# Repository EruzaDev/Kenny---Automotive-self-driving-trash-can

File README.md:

# KENNY lightweight RL environment

A runnable Gymnasium navigation simulator and PPO training pipeline for a small indoor robot. It uses height-aware boxes and analytical sensor rays instead of a full physics/rendering engine, so the laptop does not need Gazebo, ROS, or GPU rendering during training.

**This is a training environment, not a validated autonomous robot controller.** The simulator approximates LiDAR, depth, marker localization and wheel motion. Use it for learning and debugging, then validate in Gazebo and on guarded hardware before deployment. The current ROS/robot roadmap is in [the robot setup guide](docs/RL_TRAINING_AND_ROBOT_GUIDE.md).

The [0.60, 0.80, and 1.00 m/s simulation checkpoints](runs/faster-noise-moving-pilot-20261010/README.md) are included with their loading configs, contracts, and test reports. Use `speed_100/best_guarded.zip` for the 1.00 m/s map preview; see the checkpoint notes for the separate relaxed-cruise editor mode.

For Raspberry Pi 5, follow the [installation and live 3D depth GUI guide](docs/PI5_SETUP.md). The [tested Pi status](docs/PI5_SETUP_STATUS.md) records measured results and remaining hardware issues.

For ESP32-WROOM with four encoder gearmotors and two L298N boards, see the [firmware and wiring guide](docs/ESP32_FIRMWARE.md).

For phone control over the ESP32's own Wi-Fi, use the [mobile joystick firmware and setup guide](docs/ESP32_MOBILE_CONTROLLER.md). Select direct-GPIO or carrier-PCB wiring before upload.

The [provisional Kenny carrier PCB](hardware/kenny_carrier/README.md) adds four encoder terminal blocks, MPU6050/HX711 headers, passive components and labeled silkscreen. Its module footprint needs verification; the mobile sketch supports its MCP23017 motor interface when carrier mode is selected.

## Your robot

| Parameter | Configured value |
| --- | --- |
| Body width × length | 0.23 × 0.23 m |
| Total height | 0.485 m |
| Wheel track | 0.235 m, interpreted as wheel-center to wheel-center |
| Wheel diameter | 0.080 m |
| Gearmotor | 333 RPM JGB37-520; nominal wheel surface speed ≈1.395 m/s |
| Policy speed limits | 0–0.30 m/s, ±0.60 rad/s |
| Control rate | 10 Hz |
| LiDAR approximation | Horizontal scan at provisional 0.22 m height; 72 angular bins |
| Depth approximation | 36 horizontal × 9 vertical rays, reduced to collision-height ranges |
| Markers | Floor landmarks with visibility, occlusion, missed detections and noisy pose fixes |

**Confirm whether 23.5 cm is wheel-center spacing or the gap between tyre inner edges.** Camera mounting (provisionally 0.40 m high), field of view, ranges, sensor rate, acceleration and braking are configurable assumptions, not verified X3 Pro/Astra Pro calibration values. The robot collision footprint is a conservative circle enclosing the square body. Measure wheel protrusions and caster extent too.

## Install on the laptop

Supported Python: **3.10–3.12**. The system Python on this machine is 3.14, so use the separate Python 3.10 interpreter. From this repository, using `uv`:

```bash
uv venv --python python3.10 .venv
uv pip install --python .venv/bin/python torch==2.5.1 --index-url https://download.pytorch.org/whl/cpu
uv pip install --python .venv/bin/python -e '.[train,view,test]'
source .venv/bin/activate
```

A `.venv` with these packages has already been created in this workspace. On a fresh machine without `uv`, create a standard venv with `python3.10 -m venv .venv`, activate it, then use `python -m pip install` in place of `uv pip install --python .venv/bin/python`.

The CPU wheel avoids installing a large CUDA stack on your 8 GB laptop. SB3 specifically recommends CPU execution for small PPO MLPs; the RTX 2050 is optional here. Pinning PyTorch 2.5.1, SB3 2.4.1 and Gymnasium 1.0.0 keeps the tested API combination reproducible. [SB3 PPO guidance](https://stable-baselines3.readthedocs.io/en/master/modules/ppo.html), [PyTorch version-specific installers](https://pytorch.org/get-started/previous-versions/)

## Preview and validate

```bash
# Windowed top-down view: debug route follower, not a trained agent.
python -m kenny_rl.demo --stage full --seed 42

# No window required; creates a PNG.
python -m kenny_rl.demo --stage full --snapshot artifacts/world.png

# Headless speed/RAM check, followed by functional tests.
python -m kenny_rl.benchmark --steps 1000 --stage full
python -m pytest -q

# A very short end-to-end installation check, NOT navigation training.
python -m kenny_rl.train --config configs/smoke.json --run runs/my-smoke
```

You can also request a specific goal, for example:

```bash
python -m kenny_rl.demo --stage empty --start 1 1 --goal 8 9 --steps 1200
```

Coordinates are meters from the synthetic room's lower-left boundary; `(0,0)` is a wall corner here, so the robot cannot spawn there. Your real marker-map origin can be elsewhere: translate the site map and landmarks consistently. Custom points are rejected if occupied; connectivity is guaranteed for generated missions, but not for arbitrary manual goals.

In the view: grey = walls, teal = chairs, brown = low bags, purple = overhangs, orange = moving people, black/red = floor gaps, yellow squares = markers, blue circle = robot, red cross = estimated position, green star = goal. The drawn route is computed from the structural map and observed hazards; it can initially cross unseen clutter or a hidden drop.

Rendering is optional and off in all training workers. For a headless machine with an unwritable home cache, set `MPLCONFIGDIR=/tmp/kenny-mpl` before creating a snapshot.

## Train progressively

Start with one environment and the laptop configuration:

```bash
python -m kenny_rl.train --config configs/laptop.json --run runs/empty-0 --stage empty --steps 100000 --seed 0
```

This is a starting experiment budget, not an assertion that 100,000 transitions will converge. Look at validation success, collisions, timeouts and interventions. Train longer if necessary; do not advance merely because the command finished.

Resume the actor/critic and optimizer into a **new** output directory. The environment's random episode stream starts from the new seed, so this is training continuation, not bit-for-bit mid-episode replay:

```bash
python -m kenny_rl.train --config configs/laptop.json --run runs/static-0 --resume runs/empty-0/final.zip --stage static --steps 200000 --seed 0
```

Proceed through these stages, retaining and evaluating earlier checkpoints:

| Stage | What the world contains |
| --- | --- |
| `empty` | Room boundary; shorter randomized goals |
| `static` | Blocks, wall openings, turns and detours |
| `mixed` | Static layouts plus chair parts, low bags and hanging obstacles |
| `dynamic` | Mixed layouts plus walking people and periodically moved/placed bags |
| `cliffs` | Mixed layouts plus unsupported floor patches |
| `full` | All obstacle types, people, changing clutter and floor gaps |

All stages randomize positions and start/goal headings. Full worlds vary in size, layout, obstacle combinations, motor gain, slip, command delay and acceleration response. Sensor noise/dropouts and marker occlusion remain active. The curriculum is **manual**, not an automatic stage scheduler; evaluate simpler stages again to catch forgetting. Three or more independent training seeds are recommended.

For the requested larger layouts, train separate policies (or fine-tune sequentially) with the included configurations:

```bash
# 21 m × 21 m square
python -m kenny_rl.train --config configs/server_21x21.json --run runs/full-21x21-0 --seed 0

# 21 m × 10 m rectangle
python -m kenny_rl.train --config configs/server_21x10.json --run runs/full-21x10-0 --seed 0
```

`world_width` and `world_height` set the generated room axes. They default to `world_size` when absent, so older square configurations still behave unchanged. The size randomization is applied uniformly to both axes, preserving the room's aspect ratio.

### Continue reviewed mixed-stage policies on larger rooms

Use `server_mixed_21x21.json` and `server_mixed_21x10.json` to adapt existing
mixed-stage policies without simultaneously introducing pedestrians or cliffs.
These profiles preserve the avoidance reward, clearance cost, 20% simulation-only
unshielded training mixture, and paired guarded/unshielded validation. Each run
adds 250,000 transitions, with 30 validation episodes per mode every 25,000
transitions, seven workers per learner, and a 1,800-step episode limit. Dimensions
are nominal: domain randomization still varies both axes together by ±15%.

On the server, activate the training virtual environment and work from the repo
root. Ensure the previous training sweep has exited and your allocation grants
four GPUs and 32 CPUs. Use a persistent terminal such as `tmux`; detaching keeps
the launcher's session open, but does not extend a scheduler allocation.

```bash
python scripts/server_sweep.py \
  --config configs/server_mixed_21x21.json \
  --resume-from runs/server-mixed-v3-reviewed-all-gpus-continued \
  --resume-checkpoint best_guarded.zip \
  --output runs/server-mixed-21x21-reviewed \
  --seeds 0 1 2 3 --devices cuda:0 cuda:1 cuda:2 cuda:3 \
  --cpu-budget 32 --envs 7 --stage mixed --steps 250000
```

Append `--dry-run` to check all four resume artifacts/contracts without launching.
The reviewed directory contains `best_guarded.zip` for every seed; no placeholder
path or missing final checkpoint is needed. This selects each seed's guarded
best, not necessarily its newest checkpoint. Do not disable the shield on hardware.

After that sweep exits successfully, train the rectangular layout independently
from the same source checkpoints (do not run both four-GPU sweeps simultaneously):

```bash
python scripts/server_sweep.py \
  --config configs/server_mixed_21x10.json \
  --resume-from runs/server-mixed-v3-reviewed-all-gpus-continued \
  --resume-checkpoint best_guarded.zip \
  --output runs/server-mixed-21x10-reviewed \
  --seeds 0 1 2 3 --devices cuda:0 cuda:1 cuda:2 cuda:3 \
  --cpu-budget 32 --envs 7 --stage mixed --steps 250000
```

Monitor from another terminal, regardless of its working directory:

```bash
tail -n 30 -F ~/Kenny---Automotive-self-driving-trash-can/runs/server-mixed-21x21-reviewed/seed_{0,1,2,3}.log
```

Change `21x21` to `21x10` when monitoring the rectangular sweep. Output directories
must be new; the launcher refuses to overwrite one. Initial paired validation
can take several minutes before rollout tables appear. These profiles change room
size and episode budget; they do not fix the previously observed sensor-coverage
deadlocks or obstacle-command loops. Evaluate held-out worlds before deployment.

Runs contain:

- `final.zip`, periodic `checkpoints/`, and `best.zip` after the first validation.
- `config.json`, `contract.json`, dependency versions, seed and source hashes.
- `validation.jsonl` with per-episode results and aggregate metrics before training,
  periodically during training, and after the final PPO update. The final record
  can share a timestep count with a periodic record scored before that update.
- TensorBoard events, viewable with `tensorboard --logdir runs`.

`best.zip` ranks success first, then observed collision/cliff rates, intervention
fraction and reward. Dual validation selects by performance in both guarded and
unshielded modes and retains a separate `best_guarded.zip`. Small validation
samples are noisy; inspect records before selecting a release candidate.
Ctrl+C or SIGTERM during PPO training saves `interrupted.zip` and exits with
status 130. Existing run directories are rejected to avoid overwriting
experiments. Resume rejects changed robot/observation contracts; start fresh
after changing physical dimensions or sensor feature layout.

Training settings are checked before workers start; unknown settings, invalid
counts and nonfinite values are rejected. Nonfinite observations, actions or
rewards abort training rather than silently propagating through PPO. Behavior
cloning keeps demonstrations in CPU memory and transfers each minibatch to the
training device.

## Evaluate new layouts and dynamic changes

```bash
python -m kenny_rl.evaluate --model runs/static-0/final.zip --split test --stage full --episodes 100 --output artifacts/test-full.json
python -m kenny_rl.evaluate --model runs/static-0/final.zip --split stress --stage full --episodes 100 --output artifacts/stress-full.json

# Simulation-only ablation: reveals how much the guard rescues the policy.
python -m kenny_rl.evaluate --model runs/static-0/final.zip --split test --stage full --episodes 100 --unshielded --output artifacts/unshielded.json

# Watch a trained checkpoint in a newly generated world.
python -m kenny_rl.demo --model runs/static-0/final.zip --stage full --seed 700
```

The example paths must point to checkpoints you actually trained. A static-only policy is not expected to pass the full test suite; these commands illustrate how to reveal that gap.

Train/validation/test use distinct seeded random streams. Stress testing additionally introduces larger worlds and U-shaped traps not included in the training generator. A change in seed is not proof of real-world generalization; use measured school layouts in later Gazebo tests. Do not tune on the final test seeds.

A successful run must reach the goal and slow down; wall contact, cliff entry and timeouts are separate outcomes. Reports include localization error, traveled distance, interventions and clutter changes. Inspect performance by stage, and count guarded collisions as failures. Run at least 500 held-out episodes across trained seeds before considering physical validation; zero observed falls in simulation is not a safety guarantee.

## Move to the school server

Copy the source, configurations, and the complete chosen run directory. Do not copy the laptop's `.venv`. Create a fresh Python 3.10–3.12 environment on the server and install the same package versions.

First test the CPU configuration, increasing from two workers to eight only after checking CPU availability and memory:

```bash
python -m kenny_rl.train --config configs/server.json --envs 2 --run runs/server-check --stage full --steps 4096
python -m kenny_rl.train --config configs/server.json --run runs/server-0 --resume runs/static-0/final.zip --stage full --steps 1000000
```

Server defaults: up to 8 spawned simulation workers per GPU learner, 512 rollout steps per worker, 512-sample minibatches, 2 conservative PPO epochs, and target KL 0.005. The sweep launcher defaults to four CUDA devices and four independent seeds, scales worker counts to CPU allocation, and checks CUDA before starting. Training is headless. See the [sim-to-real audit and server instructions](docs/SIM_TO_REAL_AUDIT.md) for disturbance settings, transfer gaps, installation and curriculum continuation.

**Four A5000s do not automatically accelerate a single SB3 PPO learner.** This implementation can run four independent seeds/experiments, one per device. It does not implement synchronous multi-GPU PPO, and the geometric simulator remains CPU-based. Start with one server job; check the school's scheduler/resource rules before launching more.

For a fresh server experiment, first learn basic goal reaching with
`configs/server_bootstrap.json`. It uses empty geometry without dynamics or
sensor disturbances and shorter episodes. Advance only after held-out validation
shows that PPO can stop at the goal. Then resume into `configs/server.json` on
the empty stage to add measured-motion surrogates, noise, dropout, delays and
outage bursts. `best.zip` prioritizes successful navigation, then observed
collision/cliff rate and intervention rate; release evaluation still requires
zero observed contacts.

For GPU experiments, install the matching CUDA build in a fresh server environment. The following is the official CUDA 12.4 wheel family for the pinned PyTorch version; first verify the server's NVIDIA driver supports it:

```bash
uv pip install --python .venv/bin/python torch==2.5.1 --index-url https://download.pytorch.org/whl/cu124
uv pip install --python .venv/bin/python -e '.[train,view,test]'
.venv/bin/python -c 'import torch; print(torch.cuda.is_available(), torch.cuda.device_count())'
```

Then preview the commands before scheduling a sweep:

```bash
python scripts/server_sweep.py --output runs/a5000-sweep --stage empty --dry-run
# When resources are allocated, repeat without --dry-run to execute.
```

The sweep starts independent runs from scratch, or continues per-seed checkpoints with `--resume-from runs/previous-sweep`. Eight workers plus one learner per GPU needs 36 CPU slots; on 32 allocated slots the launcher selects seven workers/run. Use `--cpu-budget` to specify a scheduler allocation not reflected in CPU affinity, or `--envs` for an explicit worker count. Use `--devices cpu` for sequential CPU seed experiments. Model weights are portable between CPU and CUDA. Start fresh with the v3 contract: older checkpoints are rejected because route progress, rewards and guard behavior changed.

### More than four independent training jobs

The default remains one learner per device. `--jobs-per-device 2` enables eight
simultaneous learners on four GPUs; extra seeds queue and use the next free slot.
CPU workers are budgeted across active slots, including configured Torch threads,
and idle slots are not reserved when there are fewer seeds. Output directories
must be new. Each seed has its own checkpoints and log; `sweep.json` records actual
device assignments. No existing run or model is overwritten.

```bash
python scripts/server_sweep.py \
  --config configs/server_mixed_21x21.json \
  --output runs/mixed-21x21-eight-candidates \
  --stage mixed --seeds 0 1 2 3 4 5 6 7 \
  --devices cuda:0 cuda:1 cuda:2 cuda:3 \
  --jobs-per-device 2 --cpu-budget 32 --steps 250000 --dry-run
```

Remove `--dry-run` only after reviewing the commands and allocating the resources.
On 32 CPUs with one Torch thread per learner, this selects **three workers/run**,
not seven. This example starts from scratch: `--resume-from` requires matching
checkpoints for *every* requested seed, so a four-seed source cannot resume eight
seeds. Sharing GPUs does not guarantee higher throughput; benchmark a short sweep
in a separate output directory first and watch `nvidia-smi`, RAM, and rollout FPS.
Do not run this alongside the existing four-job sweep on the same allocation.
Pick candidates using validation results, then evaluate the selected candidate on
held-out worlds; repeatedly selecting on test results makes that test set a tuning set.

### Compare baseline and experimental candidate episodes

Keep the original controller/report as the baseline and save the revision's
evaluation to a separate file. Before changing the controller or retraining,
compare full evaluation JSON files containing `records`, not pasted summaries:

```bash
python scripts/compare_evaluations.py \
  --baseline artifacts/seed3-baseline-test.json \
  --candidate artifacts/seed3-experimental-test.json \
  --output artifacts/seed3-paired-comparison.json
```

Replace these input filenames with the reports you actually saved. The command
reads both reports without changing them and refuses to overwrite any output.
It requires matching episode seeds and evaluation settings, lists newly introduced
timeouts, lost successes, recovered successes, persistent failures and new safety
events, and saves intervention reasons for changed/failed episodes. Equal aggregate
success rates can hide different failures. The model, simulator version and room
configuration must also match for a controller-only comparison; those are not all
encoded in older report files. Reproduce regressions on development seeds, then use
fresh held-out seeds to confirm improvements. Keep the shield enabled on hardware.

## What generalizes, and what still needs validation

For a policy with poor unshielded performance, the experimental
[shield-dependence training profile](docs/SHIELD_TRAINING.md) mixes shielded and
unshielded simulation episodes, separates obstacle and sensor penalties, and
validates both modes. It preserves a separate best guarded checkpoint.

For static-stage policies with frequent shield stops, see
[static recovery](docs/STATIC_RECOVERY.md): optional clearance-aware routing,
per-cause intervention diagnostics, and a v3-compatible resume configuration.

An optional [progressive mapping mode](docs/PROGRESSIVE_MAPPING.md) now trains
with structural walls initially unknown. It provides sensor-based grid mapping,
conventional frontier selection and replanning, plus a revised final-approach
reward. Use `configs/server_progressive.json` to fine-tune v3 checkpoints. This
is a simulation surrogate; real SLAM and landmark localization still need integration.

The actor sees local range features, route-relative coordinates, estimated motion and localization health—not a fixed school map, marker ID sequence, hidden obstacles or perfect simulator pose. Global A* routing allows detours that temporarily increase straight-line goal distance. Moving people and relocated bags force fresh local responses and periodic replanning.

The default `map_mode="known"` assumes a supplied structural wall map for the current site. The optional `progressive` mode reveals a grid from sensor observations and explores frontiers. Both assume a localized start and a goal in the same coordinate frame. Neither implements a complete hardware SLAM stack. Unknown clutter and cliffs are revealed through sensor surrogates.

Important fidelity limits:

- Geometric depth rays approximate collision-height features; no RGB rendering, real ArUco image detection, material/lighting model, or Orbbec driver runs here.
- Wheel motion has acceleration, gain/slip variation and delay, but no electrical motor simulation, encoder pulse model, actual PID firmware, suspension, tipping or full rigid-body physics.
- Cliff events use intersection of the conservative footprint with a missing-floor rectangle; the robot does not physically fall in this simulator.
- The simulated guard uses measured features, not hidden geometry, and can miss hazards. Three downward sensor surrogates assume **additional physical cliff sensors**; the original LiDAR/Astra pair is insufficient as the sole cliff safeguard.
- Dynamic-object memory expires; it is not a production tracking or occupancy-fusion system. A blocked route stops and replans; autonomous recovery and hand-command handling are not implemented here.
- No ROS node or ONNX exporter is included yet. A ROS adapter must reproduce `contract.json`, frame ordering, sensor calibration, fixed normalization and action scaling, then pass Gazebo and hardware timing/safety tests.

See [the simulator design and validation notes](docs/LIGHTWEIGHT_SIMULATOR.md) for the observation contract, reward and measured checks.

## Measured environment maps

### Experimental stall recovery

Pass `--recovery` to `kenny_rl.evaluate` to test stationary scan recovery with an
existing checkpoint. After three seconds without translation, the controller
requests a slow in-place turn to reacquire markers and observe blocked routes.
Floor and downward-sensor interlocks remain active. Recovery is off by default;
it changes the controller behavior and needs paired held-out evaluation before
being enabled for training or deployment.

Guarded turns wait until measured translation is below 0.01 m/s. Recovery
remembers depth returns for 15 seconds for local braking, and
limits forward speed using their clearance, braking distance, sensor latency,
and localization uncertainty. Open-space turns use the usual 0.55 rad/s
turn-before-translate threshold. The blanket recovery threshold of 0.20 rad/s
was removed after it reduced held-out success from 81% to 76%.
The original 100-episode recovery experiment introduced a bag collision on
seed 20042. The revised controller avoids that reproduced contact, but still
times out on that seed; completion and safety must be reassessed on all 100
episodes rather than inferred from this regression case.

Replay representative failures with and without recovery:

```bash
python -m scripts.review_recovery --model runs/server-mixed-21x21-reviewed/seed_3/best_guarded.zip --output artifacts/recovery-paired.json
```

The separate `--route-recovery` candidate preserves the previous `--recovery`
behavior when absent. It scans for two seconds, then attempts route alignment
and at most 0.12 m/s forward motion for the remainder of an eight-second cycle.
It starts scanning before localization uncertainty reaches the hard stop;
uncertain localization, absent routes, and all existing sensor interlocks still
prevent translation. No stale obstacle is deleted to force progress. This is an
experimental fallback, not a replacement for validating the learned policy.
The localization-only early look now has a **hard two-second deadline**;
stall-triggered scan/route attempts have a **hard eight-second deadline**, even
if no marker is found. Both enforce an eight-second retry cooldown. A failed
early look is not rearmed by uncertainty alone: it needs a new marker correction;
an actual stall may still trigger a bounded retry after cooldown. Returning to
the policy never bypasses the unchanged hard localization/sensor guard. This
fixes the previous release condition that waited indefinitely for uncertainty
to fall below 0.10 and could keep spinning for the rest of the episode.
In a 12-case development replay, the deadline/cooldown fix recovered five of
the seven newly regressed seeds (20011, 20027, 20031, 20039, 20062), retained
success on 20060, 20084 and 20085, but lost the prior recovery of 20074. Seeds
20041, 20099 and the bag regression 20042 still timed out. No collision or cliff
was observed in these 12 cases. This fixes the unbounded override, not all
navigation failures; reassess the whole comparison set and fresh held-out seeds.
Use a new output filename to preserve previous reports:

```bash
python scripts/review_recovery.py \
  --model runs/server-mixed-21x21-reviewed/seed_3/best_guarded.zip \
  --seeds 20017 20060 20074 20084 20085 20042 \
  --recovery-only --route-recovery --snapshot-every 10 \
  --output artifacts/seed3-route-bounded-replay.json

python -m kenny_rl.evaluate \
  --model runs/server-mixed-21x21-reviewed/seed_3/best_guarded.zip \
  --episodes 100 --split test --stage mixed --route-recovery \
  --output artifacts/seed3-route-bounded-test.json
```

Compare the bounded report with `seed3-clearance-recovery-test.json` using
`scripts/compare_evaluations.py`; preserve both files and inspect seed outcomes.

A separate `--marker-sweep` candidate implies route recovery but leaves the
83%-success bounded revision unchanged when absent. Localization scans start
at uncertainty 0.15, brake before rotating, request at most 0.5 rad/s, and keep
one direction until a marker is reacquired, measured rotation reaches one full
turn, or the hard 20-second deadline expires. Floor/downward interlocks and the
hard localization stop remain unchanged; an unsuccessful scan never resets
uncertainty. The controller does not read hidden marker positions. Offline
geometry checks are diagnostic only. This candidate addresses interrupted
heading coverage, not missing markers or a production localization stack.
Low-uncertainty route alignment does not consume the candidate's separate
marker-scan opportunity. The 11-case development replay recovered 20008, 20012,
20074 and 20082 but regressed 20011, 20039 and 20062. Seeds 20027, 20031 and
20068 retained success; 20042 still timed out. This is seven successes versus
six for the bounded baseline on this selected sample, with no observed collision
or cliff. It is not an unbiased estimate of overall success or safety.

```bash
python -m kenny_rl.evaluate \
  --model runs/server-mixed-21x21-reviewed/seed_3/best_guarded.zip \
  --episodes 100 --split test --stage mixed --marker-sweep \
  --output artifacts/seed3-marker-sweep-test.json
```

Compare this report with the preserved `seed3-route-bounded-test.json`. Do not
retrain or deploy based only on selected development failures; use fresh seeds
after checking the paired outcomes and safety metrics.

Before the deadline/cooldown fix, local replay with seed 3's reviewed
`best_guarded.zip` recovered 20060, 20074,
20084 and 20085 (1099, 1269, 529 and 686 steps), with no observed collision or
cliff in these six cases. Seeds 20017 and 20042 still timed out. In particular,
20017 lost valid floor coverage during its route attempt, so the interlock
stopped it; this is not a complete fix or evidence of overall safety improvement.

The initial four-case comparison recovered seeds 20001 and 20017 with no
collisions, but 20018 and 20037 still timed out. This targeted sample does not
establish an overall success or safety improvement. Test the same 100-episode
set using `--recovery` and compare it with the baseline before selecting it.
The clearance-memory revision was checked on seeds 20042, 20017, 20001 and
20002: 20001 and 20002 succeeded; 20042 and 20017 timed out, with no collisions.
This also shows that the earlier success on 20017 did not survive the revision.

Rectangular failure replays must use the same nominal dimensions as evaluation;
the output filename does not configure the room. For example:

```bash
python scripts/review_recovery.py \
  --model runs/server-mixed-21x21-reviewed/seed_3/best_guarded.zip \
  --seeds 50002 50028 50040 50071 50091 \
  --world-width 21 --world-height 10 \
  --recovery-only --marker-sweep --snapshot-every 10 \
  --output artifacts/seed3-21x10-sensor-diagnostics.json
```

Overrides leave the checkpoint config and domain randomization unchanged.
Reports include nominal and actual room dimensions and per-snapshot sensor
validity fractions. In the corrected seed-50000 rectangular failure replay,
50028 never translated; 50040, 50071 and 50091 also reached stationary poses
with invalid floor coverage. Zero-dropout geometric checks at their final
poses gave valid floor fractions of 0.25, 0.417, 0.417 and 0.417 respectively,
below the 0.5 interlock threshold. These are coverage/occlusion stops, not
evidence that weakening the interlock is safe. Seed 50002 had no detectable
marker at its final position across a 72-heading, zero-dropout sweep. Other
failures retain good localization but show obstacle or no-route deadlocks;
these checks do not establish a controller fix or hardware safety.

The sibling [Kenny Environment Studio](../kenny-map-editor/README.md) can create measured maps, place ArUco landmarks and obstacles, and capture ROS scan maps. Load an exported `environment.json` with `python -m kenny_rl.demo --environment /path/environment.json`, or pass `--environment` to evaluation. Rectangular maps retain their actual width and height. Exported maps use ROS world coordinates; demo start/goal overrides use simulator coordinates after transforming by the inverse grid origin. The original map origin and full marker metadata remain available on the loaded world.

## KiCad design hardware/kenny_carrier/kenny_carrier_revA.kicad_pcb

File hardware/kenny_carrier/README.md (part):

# KENNY ESP32 carrier PCB — provisional Rev A

**Editable, routed two-layer prototype design. Not yet fabrication-approved.**
The owner selected a provisional footprint because the actual 38-pin ESP32
module dimensions and model/pin ordering are not available. Print/check the
socket pattern and verify the actual modules before ordering boards.

## What is on the board

- **118 × 125 mm**, 2 copper layers, nominal 1.6 mm FR-4 / 1 oz copper.
- Two 19-position female sockets for a **classic ESP32-WROOM DevKit**.
  Assumed 2.54 mm pin pitch and **25.40 mm row-center spacing**.
- Four **4-position, 5.08 mm pitch screw terminals**, one per motor encoder.
- 2.54 mm Dupont headers for an external **MPU6050 module** and **HX711 module**.
- Separate front/rear L298N **7-position screw terminals**; independent control of
  each of the four motors. Driver boards and motor-power wiring are external.
- MCP23017 GPIO expander for eight direction signals; direct ESP32 PWM and
  encoder capture, with ESP32 pins available for the two additional sensors.
- AP2112K-3.3 peripheral regulator powered from the DevKit's USB-derived 5 V.
- Decoupling capacitors, encoder input RC filters, direction/PWM pull-downs,
  I²C pull-ups, reset RC and HX711 clock pull-down.
- A **2-position screw terminal** for the normally-closed E-stop signal.
- Four M3 clearance holes, a copper-free antenna region, **KENNY** text and a
  simplified monochrome robot logo based on the image supplied by the owner.
  The logo is real front silkscreen geometry, not just a preview overlay.

## Open the design

Open `kenny_carrier_revA.kicad_pro` in **KiCad 7 or later**.

| File | Purpose |
| --- | --- |
| `kenny_carrier_revA.kicad_sch` | Editable circuit schematic |
| `kenny_carrier_revA.kicad_pcb` | Routed PCB and bottom ground plane |
| `kenny_carrier_revA.kicad_pro` | Project and design rules |
| `schematic.pdf` | Readable vector schematic |
| `board-top.svg` / `.png` | Top copper and silkscreen preview |
| `board-preview.svg` / `.png` | Green-background layout preview |
| `assembly.svg` | Component references and fabrication outlines |
| `BOM.csv` | Values, footprints and component notes |
| `circuit.json` | Machine-readable pin/net/placement specification |
| `Kenny.pretty/` | Local provisional 38-pin footprint |
| `DRC.txt`, `validation.json` | Actual check results and limitations |
| `review_gerbers/` | Provisional Gerber/drill exports; NOT approved to manufacture |

Standard footprints require the KiCad footprint libraries. The included
`fp-lib-table` uses `KICAD7_FOOTPRINT_DIR`; on another version, point that variable
at the installed footprint directory in Preferences → Configure Paths.
All footprint geometry is also embedded in the PCB file.

## Motor encoder terminals

The user confirmed **4-pin encoder terminals**, so the red/white motor winding
wires do **not** pass through this carrier. They go directly to the L298N output
terminals as described below.

| Terminal | Motor |
| --- | --- |
| **J1** | Left-front encoder |
| **J2** | Right-front encoder |
| **J3** | Left-rear encoder |
| **J4** | Right-rear encoder |

Every encoder terminal uses this order, top-to-bottom in the top-view preview:

| Position | Signal | Supplier wire color |
| --- | --- | --- |
| **1** | **+3.3 V** encoder power | Blue |
| **2** | **GND** | Black |
| **3** | **A** | Yellow |
| **4** | **B** | Green |

The selected footprint is **Phoenix MKDS 1,5/4-5.08**, horizontal wire entry
toward the board's left edge, drill 1.3 mm. Match the purchased terminal's
mechanical drawing to this footprint; generic 5.0 mm and 5.08 mm blocks are
not automatically interchangeable.

Encoder A/B each pass through a **1 kΩ series resistor** into the ESP32 input,
with **1 nF C0G to GND** on the ESP32 side: nominal 1 µs RC. This is noise
filtering, **not 5 V level conversion or ESD certification**. The identified
supplier's encoders support a 3.3 V supply and include output pull-up circuitry.
If a different encoder is fitted, verify its output type/voltage first.

## Sensor Dupont headers

The square pad is pin 1. Wire **by signal**, not by blindly matching the physical
order of another module's connector. Headers are unkeyed; check polarity.

| Header | Pin 1 | Pin 2 | Pin 3 | Pin 4 |
| --- | --- | --- | --- | --- |
| **J5 MPU6050** | 3V3 | GND | SDA | SCL |
| **J6 HX711** | 3V3 | GND | DOUT / DT | SCK |

- MPU6050 I²C defaults to **0x68** when AD0 is low (0x69 if high). Tie AD0 on
  the module according to its documentation; this four-wire header does not
  carry AD0 or INT. Polling is supported. Use a module that operates correctly
  from the provided 3.3 V input; some boards expose a regulator VIN with dropout.
- MCP23017 address pins are grounded for **0x20**, so it does not conflict with MPU6050.
- HX711 is an **external amplifier board**, not the bare four-wire load cell.
  The load cell connects to that module's E+/E− and A+/A− inputs according to
  the load-cell datasheet. HX711 is not I²C. Use 3.3 V-compatible module power,
  excitation and DOUT logic; calibrate tare and scale in software.
- R21/R22 are **4.7 kΩ SDA/SCL pull-ups** to peripheral 3.3 V. If the MPU module
  has its own pull-ups, check the combined resistance and leave R21/R22 unpopulated
  if needed. Keep sensor cables short, start I²C at 100 kHz, and route them away
  from motor-power wires.

## L298N terminal blocks and motor connections

| Terminal block | External board | OUT1 / OUT2 | OUT3 / OUT4 |
| --- | --- | --- | --- |
| **J7 FRONT** | L298N #1 | Left-front red / white | Right-front red / white |
| **J8 REAR** | L298N #2 | Left-rear red / white | Right-rear red / white |

J7/J8 are **Phoenix PT 1,5/7-3.5-H**, 7 positions, **3.50 mm pitch**,
1.2 mm drill, with wire entry toward the right board edge. Match the purchased
part to the footprint; this is not a 5.08 mm or 2.54 mm terminal footprint.
For both J7/J8, **top-to-bottom** in the top-view preview:

| Pin | Silkscreen | Connect to L298N |
| --- | --- | --- |
| 1 | G | GND |
| 2 | EA | ENA |
| 3 | I1 | IN1 |
| 4 | I2 | IN2 |
| 5 | I3 | IN3 |
| 6 | I4 | IN4 |
| 7 | EB | ENB |

**Remove ENA/ENB jumpers on both L298N boards.** Four 10 kΩ enable pull-downs
are on the carrier; eight direction pull-downs hold the inputs low while the
MCP23017 is reset/high-impedance. There are **no shared direction signals**
between motor channels. Add pull-downs at the external driver ends too if the
driver must remain disabled when the control cable itself is disconnected.

Motor battery wiring, fused power distribution, appropriate motor-driver cooling
and physical power-cut E-stop are external. No 12 V or motor current belongs on
J1–J9. Add motor-noise suppression close to the motors as appropriate (typically
100 nF ceramic across each motor's winding terminals, rated at least 50 V) and
bulk decoupling at each external driver per its power design. These off-board
parts are not included in the carrier placement/BOM.

The supplied 333 RPM NFP-JGB37-520-EN motor is **12 V, 30:1, 2.4 A stall per motor**.
That exceeds the common L298N continuous-channel rating. This PCB is only a logic
interface and does not resolve that motor/driver sizing issue. Review or replace
the external drivers before loaded robot operation.

## Power and passive components

USB → ESP32 DevKit **5 V header pin** → AP2112K-3.3 → **+3V3 peripherals**.
The ESP32's own 3.3 V rail is separate and is used only for the E-stop pull-up.
There is no external power input or USB/external-supply selector on this carrier.

**Confirm the chosen DevKit exposes USB-derived 5 V at the assumed pin**. A pin
labeled VIN on an unknown clone is not proof that this source is available.
Use only one verified USB supply, and never bring L298N motor/5 V power back
through a logic header. There is no onboard fuse or surge/5 V encoder protection.

| References | Value/function |
| --- | --- |
| R1–R8 / C1–C8 | 1 kΩ / 1 nF encoder input filters |
| C9–C12 | 100 nF encoder connector decoupling |
| R9–R16 | 10 kΩ MCP direction pull-downs |
| R17–R20 | 10 kΩ motor-enable pull-downs |
| R21–R22 | 4.7 kΩ I²C pull-ups |
| R23 / C19 | 10 kΩ / 100 nF MCP reset RC |
| R24 | 10 kΩ ESP32 E-stop input pull-up |
| R25 | 10 kΩ HX711 SCK pull-down |
| C13 / C14 | 1 µF regulator input / 10 µF output |
| C15 | 100 nF at MCP23017 |
| C16 / C17 | 100 nF at MPU6050 / HX711 headers |
| C18 | Additional 10 µF peripheral bulk capacitance |

Use non-polar ceramic capacitors with the ratings in `BOM.csv`, and allow for DC
bias derating of 10 µF parts. Resistors/capacitors are **0805** for assembly;
U2 is SOIC-28W and U3 is SOT-23-5. The AP2112's 600 mA rating is not a guaranteed
thermal budget on this board. Start with **≤150 mA total peripheral load**;
at 5 V input that dissipates about 0.255 W. Measure encoder/module currents,
regulator temperature, USB supply drop and startup behavior before accepting it.
Test points TP1=3V3, TP2=GND, TP3=USB 5V.

J9 is a **Phoenix PT 1,5/2-3.5-H** two-position screw terminal, **3.50 mm pitch**.
It takes a normally-closed E-stop auxiliary contact: **pin 1 GND, pin 2 signal**
(left-to-right in the top view).
Open=stop. It is an input to firmware, not a hardwired motor-power disconnect.

## Firmware mapping — DIFFERENT from the direct-wire sketch

**Do not flash the existing direct-GPIO L298N sketch unchanged for this PCB.**
It uses GPIO16/17/21/22 as motor direction outputs, but this PCB uses those
pins for HX711/I²C. A matching joystick sketch is now available in
[`firmware/kenny_mobile`](../../firmware/kenny_mobile/README.md): select
`KENNY_CARRIER_MCP23017` in `config.h`. The carrier variant compiles and its
controller logic/web UI have software checks; physical tests remain pending.
This sketch reserves sensor pins but does not yet read MPU6050/HX711 measurements.

| Function | MCU connection |
| --- | --- |
| Left-front / right-front PWM | GPIO25 / GPIO26 |
| Left-rear / right-rear PWM | GPIO32 / GPIO33 |
| LF encoder A/B | GPIO34 / GPIO27 |
| RF encoder A/B | GPIO35 / GPIO14 |
| LR encoder A/B | GPIO36 / GPIO13 |
| RR encoder A/B | GPIO39 / GPIO23 |
| I²C SDA/SCL | GPIO21 / GPIO22 |
| HX711 DOUT/SCK | GPIO16 / GPIO17 |
| E-stop input | GPIO18 |
| Direction outputs | MCP23017 GPB0–GPB7, eight separate signals |

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
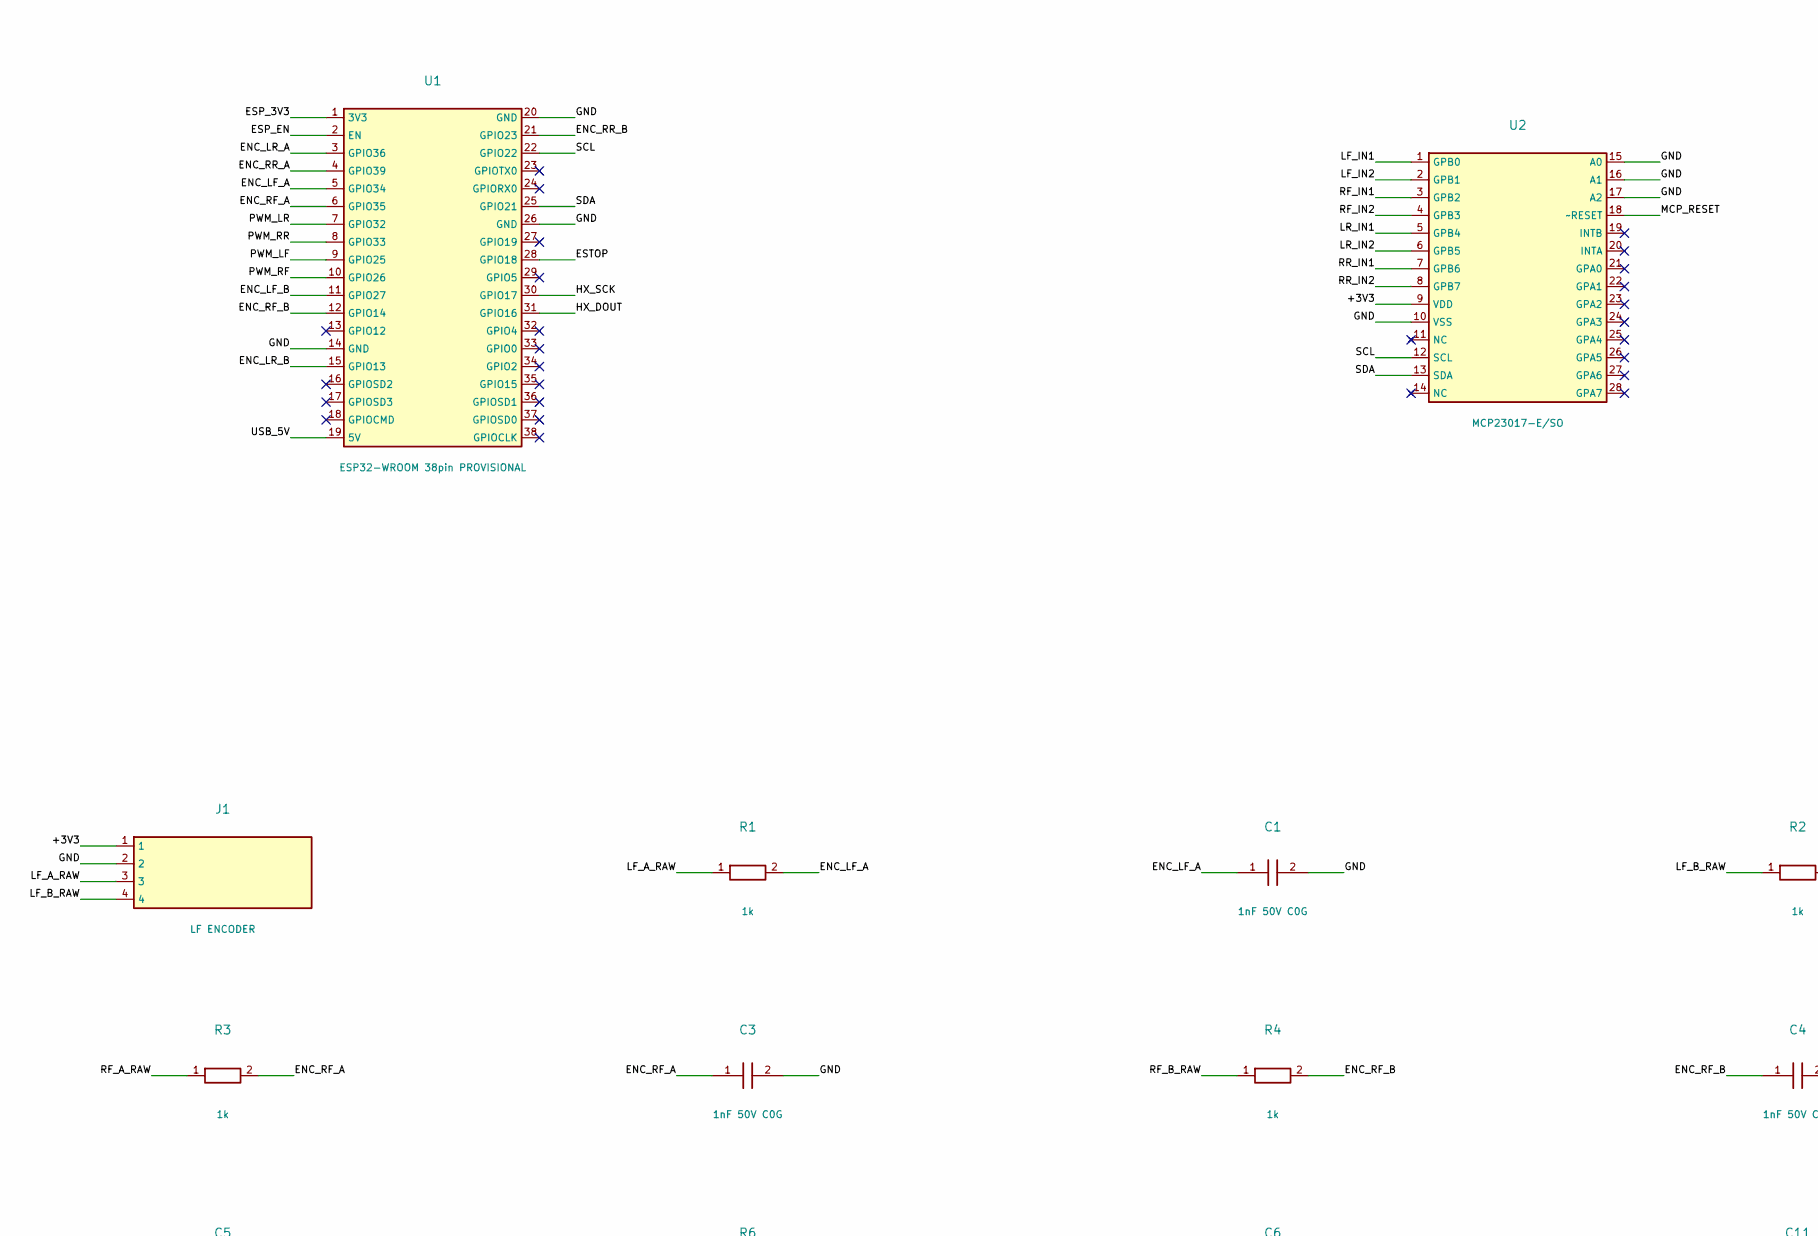
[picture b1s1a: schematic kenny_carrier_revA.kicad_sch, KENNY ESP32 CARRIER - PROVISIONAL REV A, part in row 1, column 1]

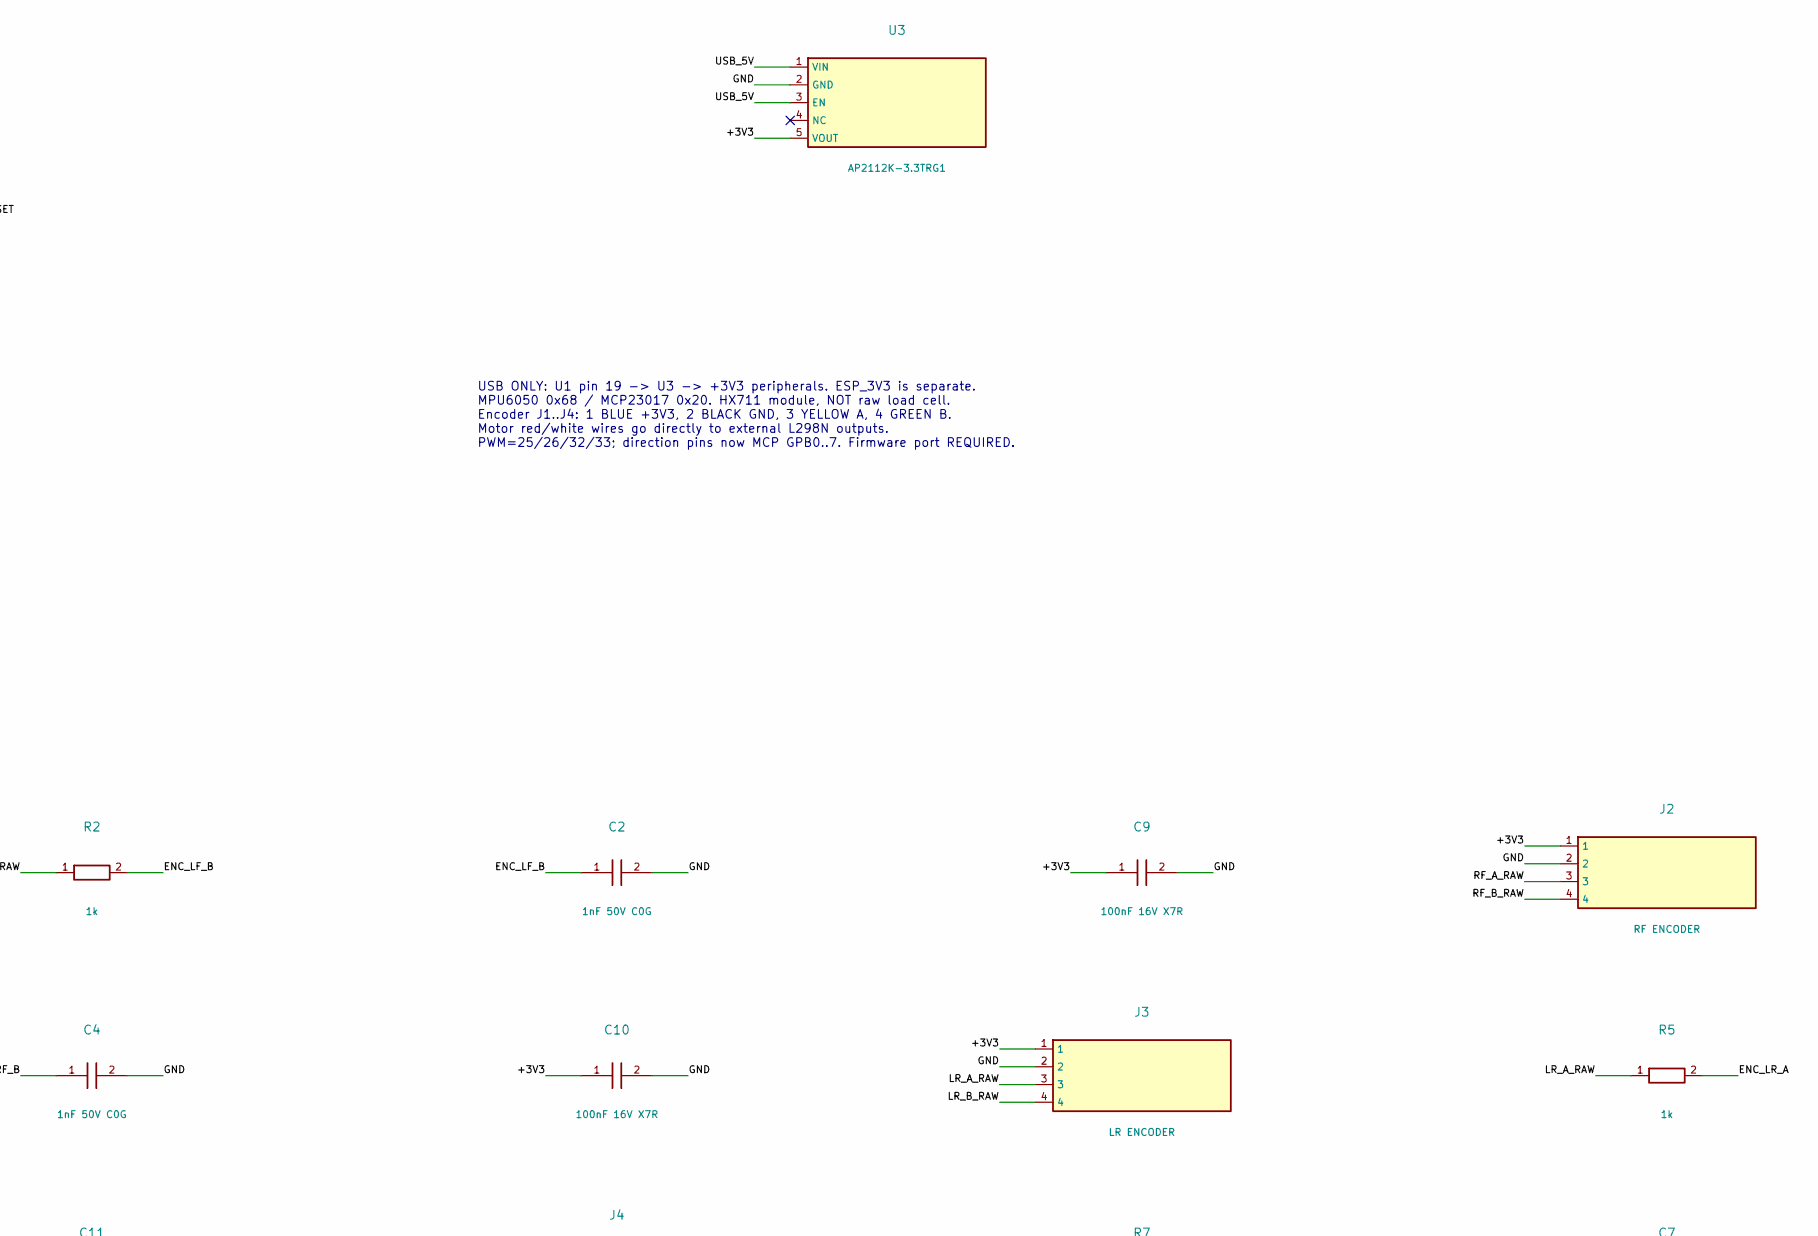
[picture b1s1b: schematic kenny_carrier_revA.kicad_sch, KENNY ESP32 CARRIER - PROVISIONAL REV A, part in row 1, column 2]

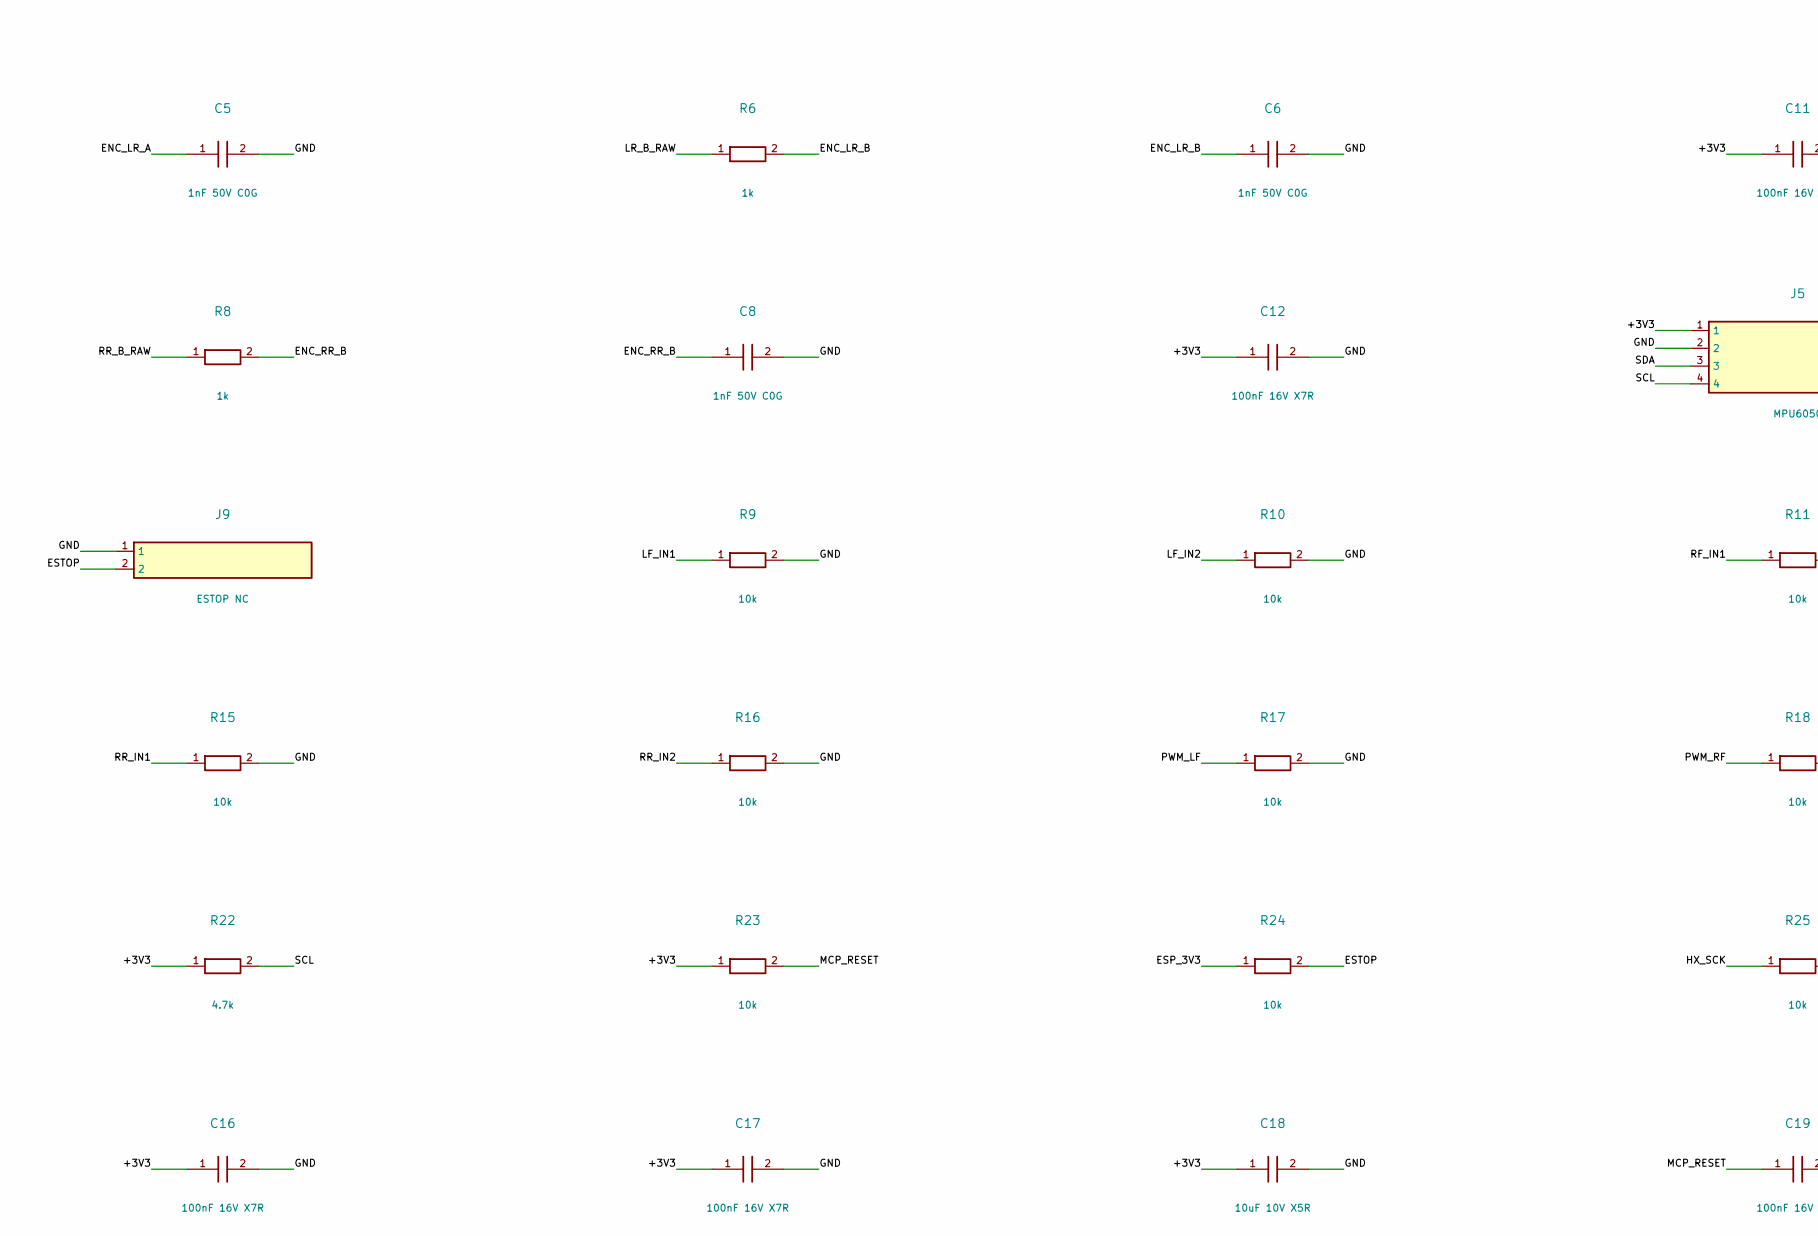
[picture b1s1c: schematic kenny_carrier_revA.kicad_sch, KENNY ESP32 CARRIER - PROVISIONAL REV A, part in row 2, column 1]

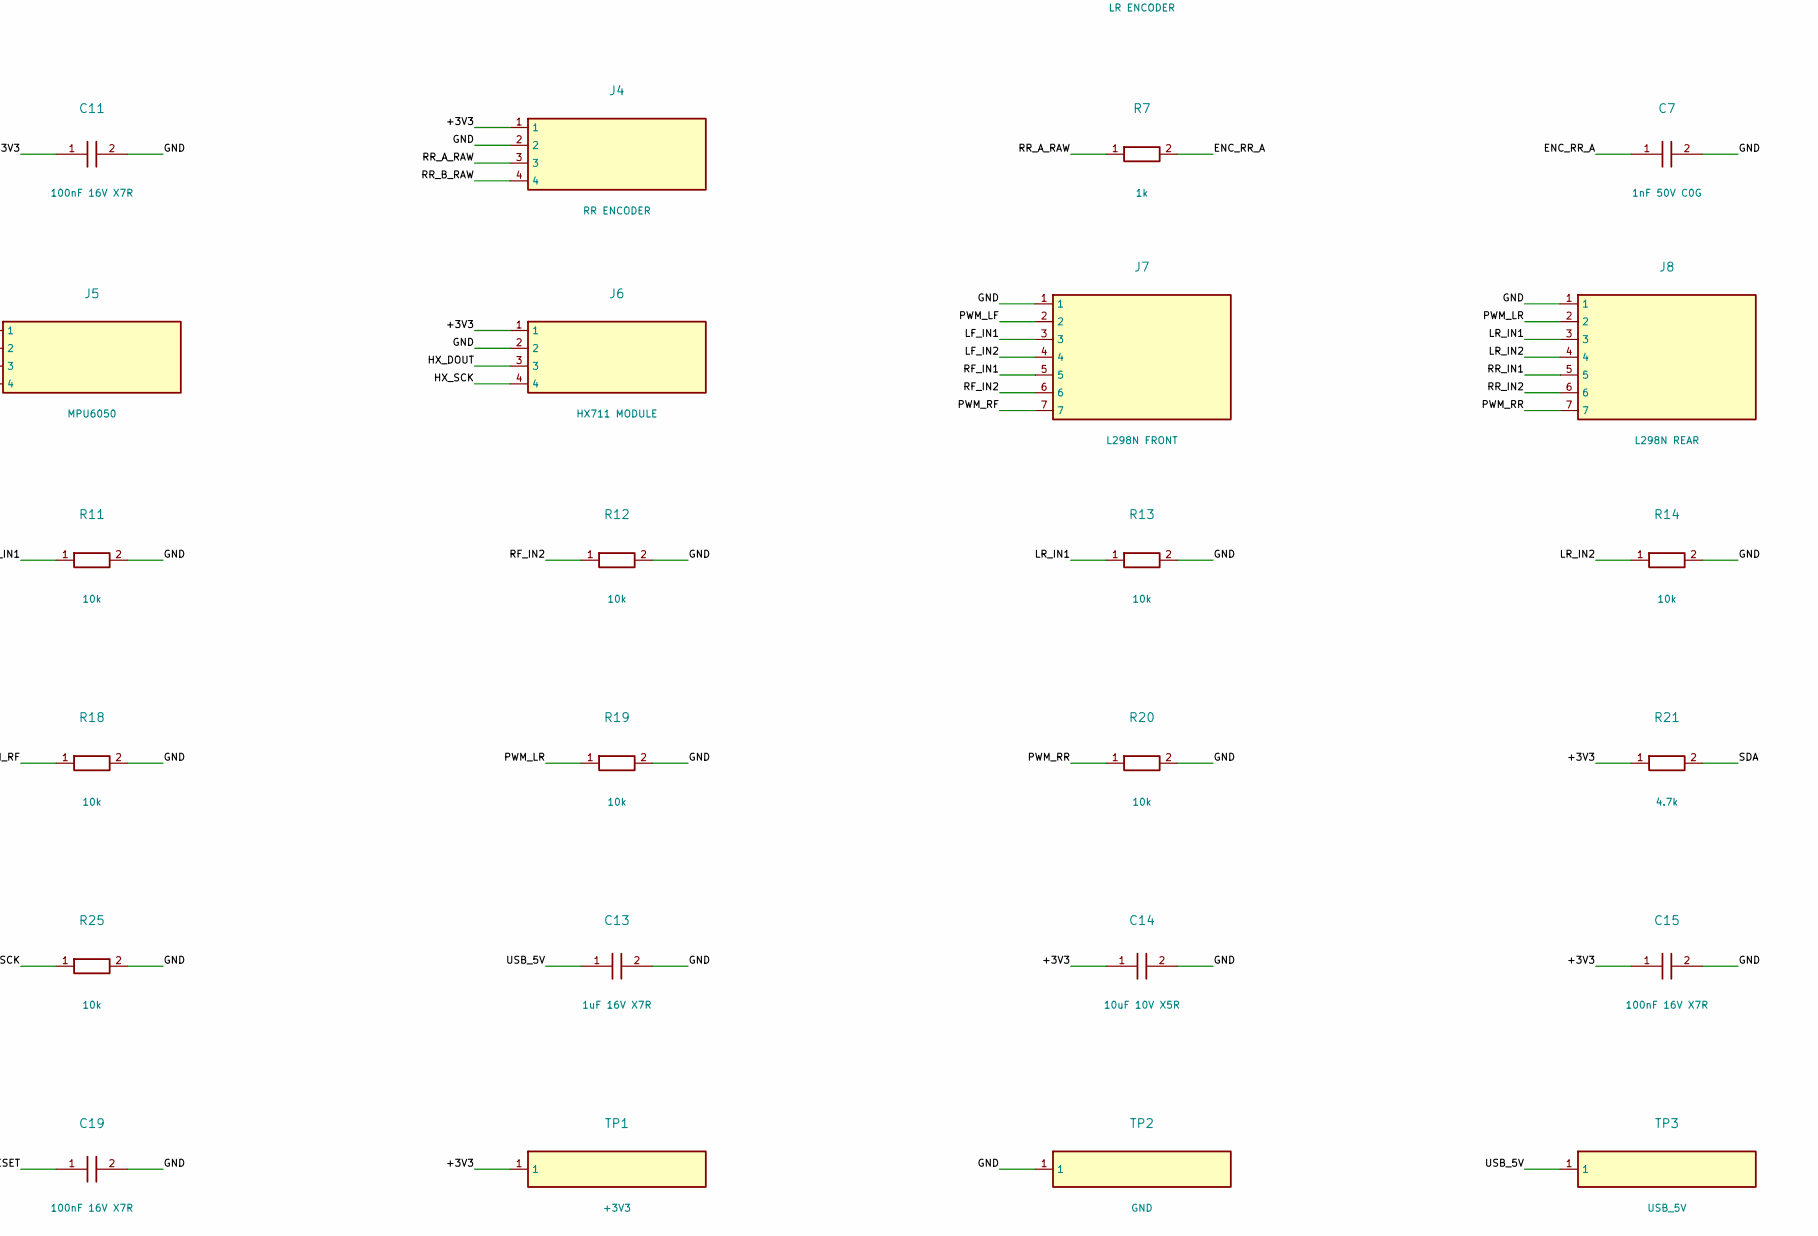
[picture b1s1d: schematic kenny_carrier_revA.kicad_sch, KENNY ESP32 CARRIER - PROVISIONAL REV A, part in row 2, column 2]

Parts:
C1, C2, C3, C4, C5, C6, C7, C8: 1nF 50V C0G; C_0805_2012Metric
C9, C10, C11, C12, C15, C16, C17, C19: 100nF 16V X7R; C_0805_2012Metric
C13: 1uF 16V X7R; C_0805_2012Metric
C14, C18: 10uF 10V X5R; C_0805_2012Metric
J1: LF ENCODER; TerminalBlock_Phoenix_MKDS-1,5-4-5.08_1x04_P5.08mm_Horizont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
J2: RF ENCODER; TerminalBlock_Phoenix_MKDS-1,5-4-5.08_1x04_P5.08mm_Horizont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
J3: LR ENCODER; TerminalBlock_Phoenix_MKDS-1,5-4-5.08_1x04_P5.08mm_Horizont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
J4: RR ENCODER; TerminalBlock_Phoenix_MKDS-1,5-4-5.08_1x04_P5.08mm_Horizont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
J5: MPU6050; PinHeader_1x04_P2.54mm_Vertical
J6: HX711 MODULE; PinHeader_1x04_P2.54mm_Vertical
J7: L298N FRONT; TerminalBlock_Phoenix_PT-1,5-7-3.5-H_1x07_P3.50mm_Horizontal
J8: L298N REAR; TerminalBlock_Phoenix_PT-1,5-7-3.5-H_1x07_P3.50mm_Horizontal
J9: ESTOP NC; TerminalBlock_Phoenix_PT-1,5-2-3.5-H_1x02_P3.50mm_Horizontal
R1, R2, R3, R4, R5, R6, R7, R8: 1k; R_0805_2012Metric
R9, R10, R11, R12, R13, R14, R15, R16, R17, R18, R19, R20, R23, R24, R25: 10k; R_0805_2012Metric
R21, R22: 4.7k; R_0805_2012Metric
TP1: +3V3; TestPoint_Pad_D2.0mm
TP2: GND; TestPoint_Pad_D2.0mm
TP3: USB_5V; TestPoint_Pad_D2.0mm
U1: ESP32-WROOM 38pin PROVISIONAL; ESP32_38_PROVISIONAL
U2: MCP23017-E/SO; SOIC-28W_7.5x17.9mm_P1.27mm
U3: AP2112K-3.3TRG1; SOT-23-5

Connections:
+3V3: C9.1, C10.1, C11.1, C12.1, C14.1, C15.1, C16.1, C17.1, C18.1, J1.1, J2.1, J3.1, J4.1, J5.1, J6.1, R21.1, R22.1, R23.1, TP1.1, U2.9 (VDD), U3.5 (VOUT)
ENC_LF_A: C1.1, R1.2, U1.5 (GPIO34)
ENC_LF_B: C2.1, R2.2, U1.11 (GPIO27)
ENC_LR_A: C5.1, R5.2, U1.3 (GPIO36)
ENC_LR_B: C6.1, R6.2, U1.15 (GPIO13)
ENC_RF_A: C3.1, R3.2, U1.6 (GPIO35)
ENC_RF_B: C4.1, R4.2, U1.12 (GPIO14)
ENC_RR_A: C7.1, R7.2, U1.4 (GPIO39)
ENC_RR_B: C8.1, R8.2, U1.21 (GPIO23)
ESP_3V3: R24.1, U1.1 (3V3)
ESP_EN: U1.2 (EN)
ESTOP: J9.2, R24.2, U1.28 (GPIO18)
GND: C1.2, C2.2, C3.2, C4.2, C5.2, C6.2, C7.2, C8.2, C9.2, C10.2, C11.2, C12.2, C13.2, C14.2, C15.2, C16.2, C17.2, C18.2, C19.2, J1.2, J2.2, J3.2, J4.2, J5.2, J6.2, J7.1, J8.1, J9.1, R9.2, R10.2, R11.2, R12.2, R13.2, R14.2, R15.2, R16.2, R17.2, R18.2, R19.2, R20.2, R25.2, TP2.1, U1.14 (GND), U1.20 (GND), U1.26 (GND), U2.10 (VSS), U2.15 (A0), U2.16 (A1), U2.17 (A2), U3.2 (GND)
HX_DOUT: J6.3, U1.31 (GPIO16)
HX_SCK: J6.4, R25.1, U1.30 (GPIO17)
LF_A_RAW: J1.3, R1.1
LF_B_RAW: J1.4, R2.1
LF_IN1: J7.3, R9.1, U2.1 (GPB0)
LF_IN2: J7.4, R10.1, U2.2 (GPB1)
LR_A_RAW: J3.3, R5.1
LR_B_RAW: J3.4, R6.1
LR_IN1: J8.3, R13.1, U2.5 (GPB4)
LR_IN2: J8.4, R14.1, U2.6 (GPB5)
MCP_RESET: C19.1, R23.2, U2.18 (~RESET)
PWM_LF: J7.2, R17.1, U1.9 (GPIO25)
PWM_LR: J8.2, R19.1, U1.7 (GPIO32)
PWM_RF: J7.7, R18.1, U1.10 (GPIO26)
PWM_RR: J8.7, R20.1, U1.8 (GPIO33)
RF_A_RAW: J2.3, R3.1
RF_B_RAW: J2.4, R4.1
RF_IN1: J7.5, R11.1, U2.3 (GPB2)
RF_IN2: J7.6, R12.1, U2.4 (GPB3)
RR_A_RAW: J4.3, R7.1
RR_B_RAW: J4.4, R8.1
RR_IN1: J8.5, R15.1, U2.7 (GPB6)
RR_IN2: J8.6, R16.1, U2.8 (GPB7)
SCL: J5.4, R22.2, U1.22 (GPIO22), U2.12 (SCL)
SDA: J5.3, R21.2, U1.25 (GPIO21), U2.13 (SDA)
USB_5V: C13.1, TP3.1, U1.19 (5V), U3.1 (VIN), U3.3 (EN)

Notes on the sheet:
USB ONLY: U1 pin 19 -> U3 -> +3V3 peripherals. ESP_3V3 is separate. MPU6050 0x68 / MCP23017 0x20. HX711 module, NOT raw load cell. Encoder J1..J4: 1 BLUE +3V3, 2 BLACK GND, 3 YELLOW A, 4 GREEN B. Motor red/white wires go directly to external L298N outputs. PWM=25/26/32/33; direction pins now MCP GP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
